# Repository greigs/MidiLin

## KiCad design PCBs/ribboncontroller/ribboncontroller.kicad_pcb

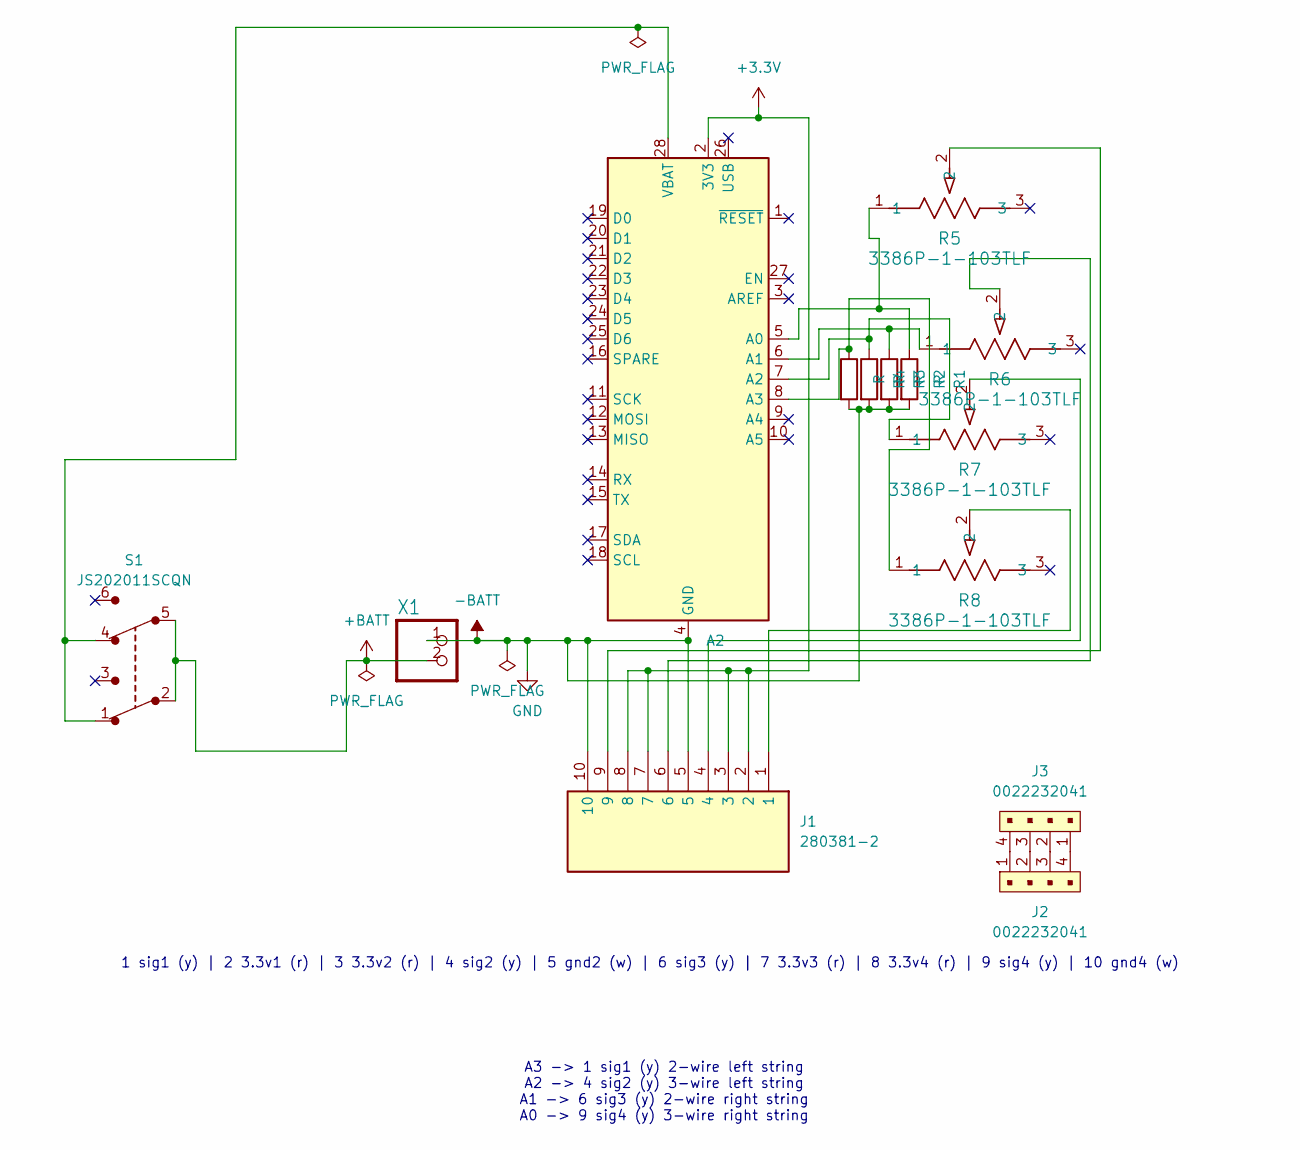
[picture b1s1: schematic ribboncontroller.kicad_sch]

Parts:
A2: Adafruit_Feather_Generic; Adafruit_Feather
J1: 280381-2; 2803812; Manufacturer_Part_Number 280381-2
J2, J3: 0022232041; PinHeader_1x4_P2.54mm_Drill1.02mm; MPN 0022232041; Digi-Key_PN WM4202-ND
R1, R2, R3, R4: R; R_0805_2012Metric_Pad1.20x1.40mm_HandSolder
R5, R6, R7, R8: 3386P-1-103TLF; POT_3386P
S1: JS202011SCQN; Switch_Slide_JS202011SCQN; MPN JS202011SCQN; Digi-Key_PN 401-2002-1-ND
X1: CON_JST_PH_2PIN; JSTPH2

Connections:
+3.3V: A2.2 (3V3), J1.2, J1.3, J1.7, J1.8
+BATT: S1.2, S1.5, X1.2
-BATT: A2.4 (GND), J1.5, J1.10, R1.2, R2.2, R3.2, R4.2, X1.1
unnamed: A2.5 (A0), R1.1, R5.1
unnamed: A2.6 (A1), R2.1, R6.1
unnamed: A2.7 (A2), R3.1, R7.1
unnamed: A2.8 (A3), R4.1, R8.1
unnamed: A2.28 (VBAT), S1.1, S1.4
unnamed: J1.1, R8.2
unnamed: J1.4, R7.2
unnamed: J1.6, R6.2
unnamed: J1.9, R5.2
unnamed: J2.1, J3.4
unnamed: J2.2, J3.3
unnamed: J2.3, J3.2
unnamed: J2.4, J3.1

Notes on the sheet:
1 sig1 (y) | 2 3.3v1 (r) | 3 3.3v2 (r) | 4 sig2 (y) | 5 gnd2 (w) | 6 sig3 (y) | 7 3.3v3 (r) | 8 3.3v4 (r) | 9 sig4 (y) | 10 gnd4 (w)
A3 -> 1 sig1 (y) 2-wire left string A2 -> 4 sig2 (y) 3-wire left string A1 -> 6 sig3 (y) 2-wire right string A0 -> 9 sig4 (y) 3-wire right string

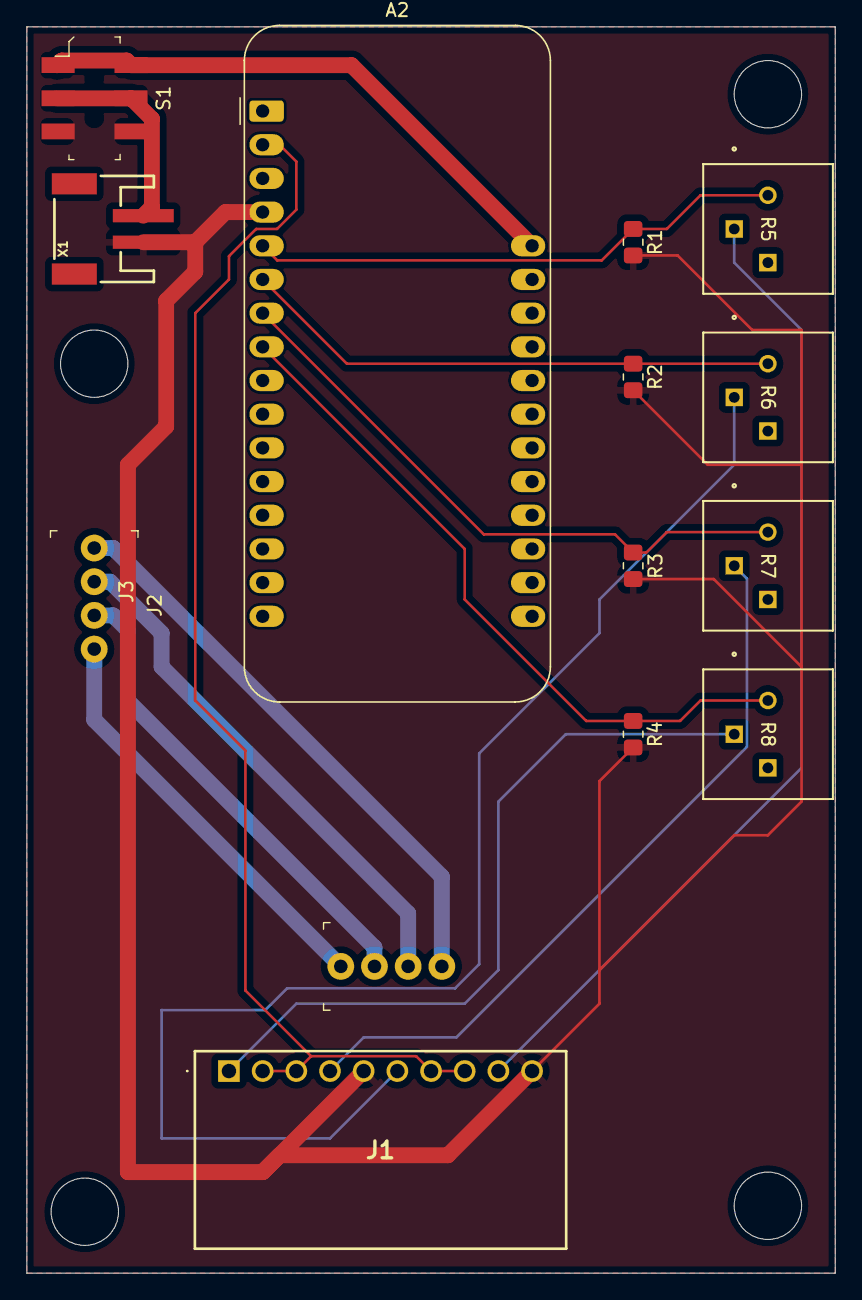
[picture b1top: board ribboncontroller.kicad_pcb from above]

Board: 2 copper layers, 61.0 x 94.0 mm, 14 parts (0 on the bottom side), 16 nets.

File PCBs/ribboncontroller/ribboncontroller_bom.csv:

"Reference","Value","Datasheet","Footprint","Qty","DNP"
"A2","Adafruit_Feather_Generic","https://cdn-learn.adafruit.com/downloads/pdf/adafruit-feather.pdf","Module:Adafruit_Feather","1",""
"J1","280381-2","https://www.te.com/commerce/DocumentDelivery/DDEController?A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","KiCad:2803812","1",""
"J2,J3","0022232041","https://www.molex.com/pdm_docs/sd/022232041_sd.pdf","digikey-footprints:PinHeader_1x4_P2.54mm_Drill1.02mm","2",""
"R1,R2,R3,R4","R","~","Resistor_SMD:R_0805_2012Metric_Pad1.20x1.40mm_HandSolder","4",""
"R5,R6,R7,R8","3386P-1-103TLF","3386P-1-103TLF","footprints2:POT_3386P","4",""
"SW1","DPDT-EG1390","","JST2 switch:EG1390","1",""
"X1","CON_JST_PH_2PIN","","JST2 switch:JSTPH2","1",""

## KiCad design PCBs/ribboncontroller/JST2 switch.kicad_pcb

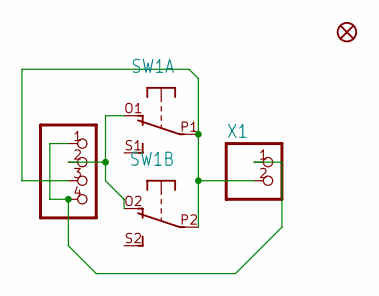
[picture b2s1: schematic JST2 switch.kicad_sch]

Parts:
FID1: FIDUCIAL""; FIDUCIAL_1MM
JP1: PADS-4
SW1: DPDT-EG1390; EG1390
X1: CON_JST_PH_2PIN; JSTPH2

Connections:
GND: JP1.1, JP1.4, X1.1
unnamed: JP1.3, SW1.P1, SW1.P2, X1.2
unnamed: JP1.2, SW1.O1 (O), SW1.O2 (O)

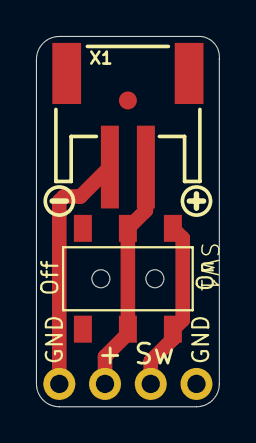
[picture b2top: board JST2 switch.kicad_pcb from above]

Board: 2 copper layers, 10.2 x 20.6 mm, 7 parts (1 on the bottom side), 3 nets.

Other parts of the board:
U$1: SYMBOL_PLUS
U$2: SYMBOL_MINUS
U$3: ADAFRUIT_5MM

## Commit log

2024-09-23 using arduino due, same wiring. EEPROM code removed
2024-09-23 using flash memory for storing calibration data. Uses 12-bit ADC stored as 16-bit
2024-09-23 storage validation fix
2024-09-23 explicitly use uint16_t
2024-09-26 working decently for my purposes, but range still needs tweaked
2024-10-10 host midi communication working
2024-10-10 midi in to host device working
2024-10-10 debug flag
2024-10-10 tidy up
2024-10-10 combined with i2c reading joypad
2024-10-11 v1 pcb submitted to manufacturer
2024-10-19 starting to consolidate code
2024-10-19 remove comments
2024-10-19 remove unused code
2024-10-19 fixed v2, removed non-legato note-on and noteoff
2024-10-19 first combined example working
2024-10-19 correct sounding range
2024-10-19 removed old version
2024-10-20 disabled both joysticks until seesaw is working again
2024-10-20 syntax fix
2024-10-20 sync kicad changes
